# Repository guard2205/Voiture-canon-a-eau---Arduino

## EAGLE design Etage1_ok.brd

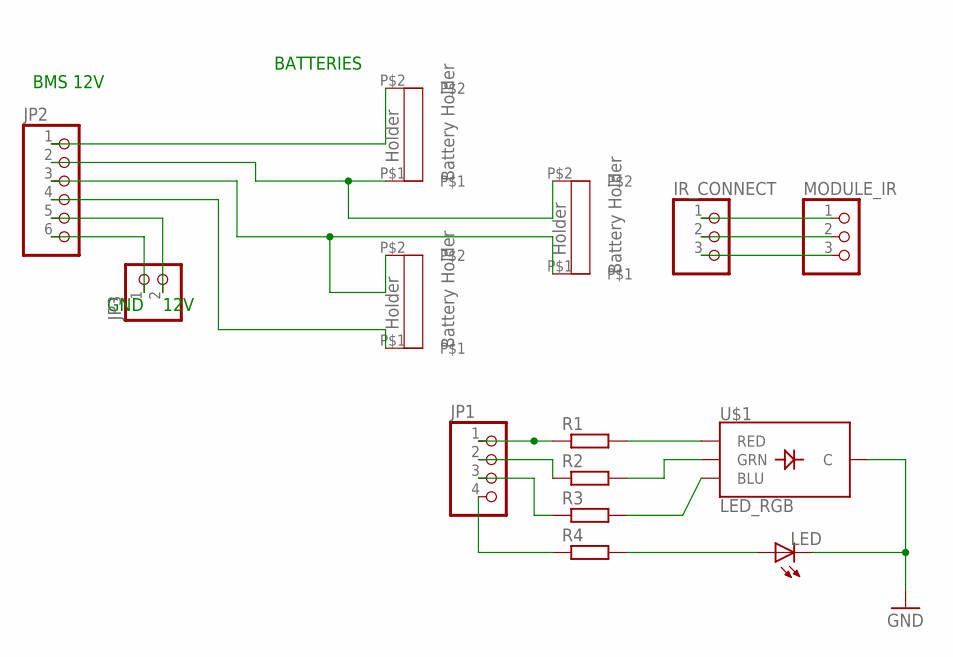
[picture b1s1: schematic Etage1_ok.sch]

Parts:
IR_CONNECT: PINHD-1X3/LONG; 1X03
JP1: PINHD-1X4/LONG; 1X04
JP2: PINHD-1X6/LONG; 1X06
JP3: PINHD-1X2/LONG; 1X02
LED: LED5MM
MODULE_IR: PINHD-1X3/LONG; 1X03
R1, R2, R3, R4: R-EU_0207/10; 0207/10
U$1: LED_RGB; LED-RGB-THRU
U$2, U$3, U$4: SUPPORT_BATTERY; BATTERY_HOLDER

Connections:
GND: LED.K (C), U$1.2 (C)
unnamed: JP2.1, U$4.P$2
unnamed: IR_CONNECT.1, MODULE_IR.1
unnamed: JP2.3, U$2.P$1, U$3.P$2
unnamed: JP2.5, JP3.2
unnamed: JP2.4, U$3.P$1
unnamed: JP2.6, JP3.1
unnamed: R1.2, U$1.4 (RED)
unnamed: R2.2, U$1.3 (GRN)
unnamed: IR_CONNECT.2, MODULE_IR.2
unnamed: JP1.1, R1.1
unnamed: R3.2, U$1.1 (BLU)
unnamed: LED.A, R4.2
unnamed: JP1.4, R4.1
unnamed: JP1.2, R2.1
unnamed: IR_CONNECT.3, MODULE_IR.3
unnamed: JP1.3, R3.1
unnamed: JP2.2, U$2.P$2, U$4.P$1

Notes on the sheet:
BATTERIES
BMS 12V
12V
GND

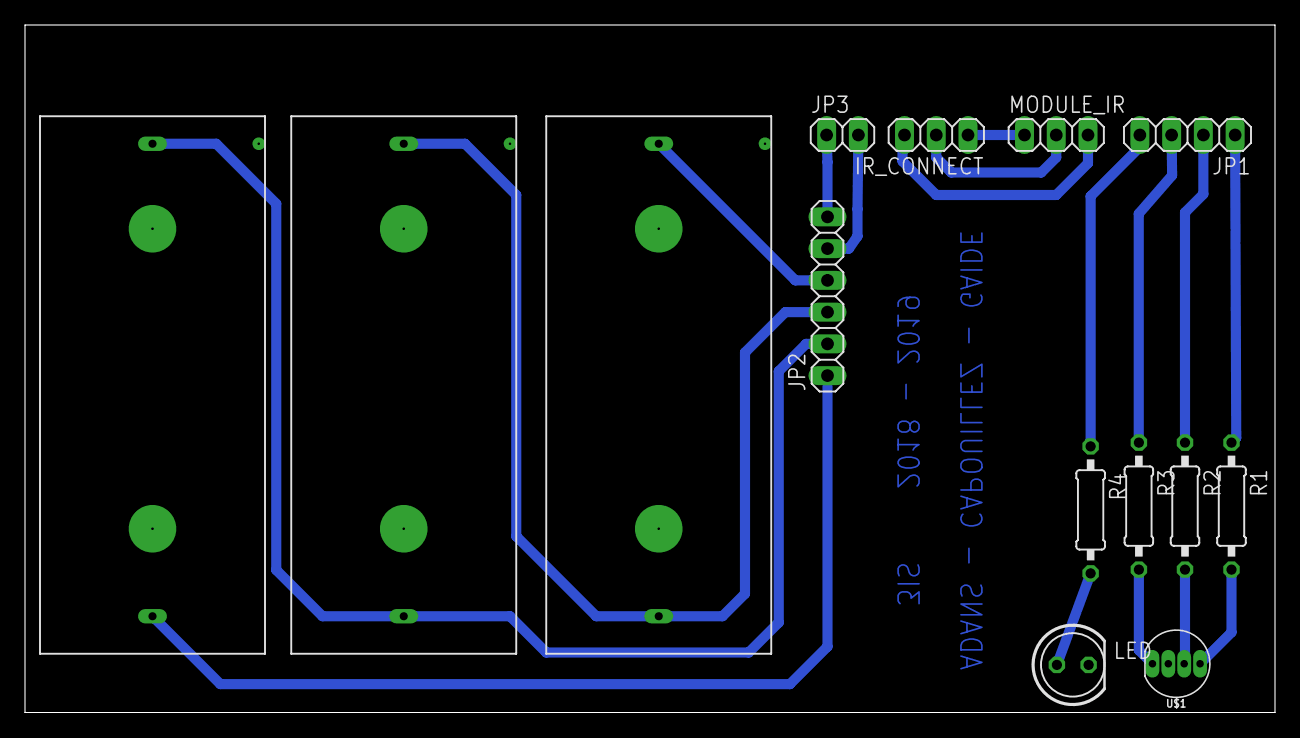
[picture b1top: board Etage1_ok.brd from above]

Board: 2 copper layers, 100.0 x 55.0 mm, 14 parts (0 on the bottom side), 18 nets.

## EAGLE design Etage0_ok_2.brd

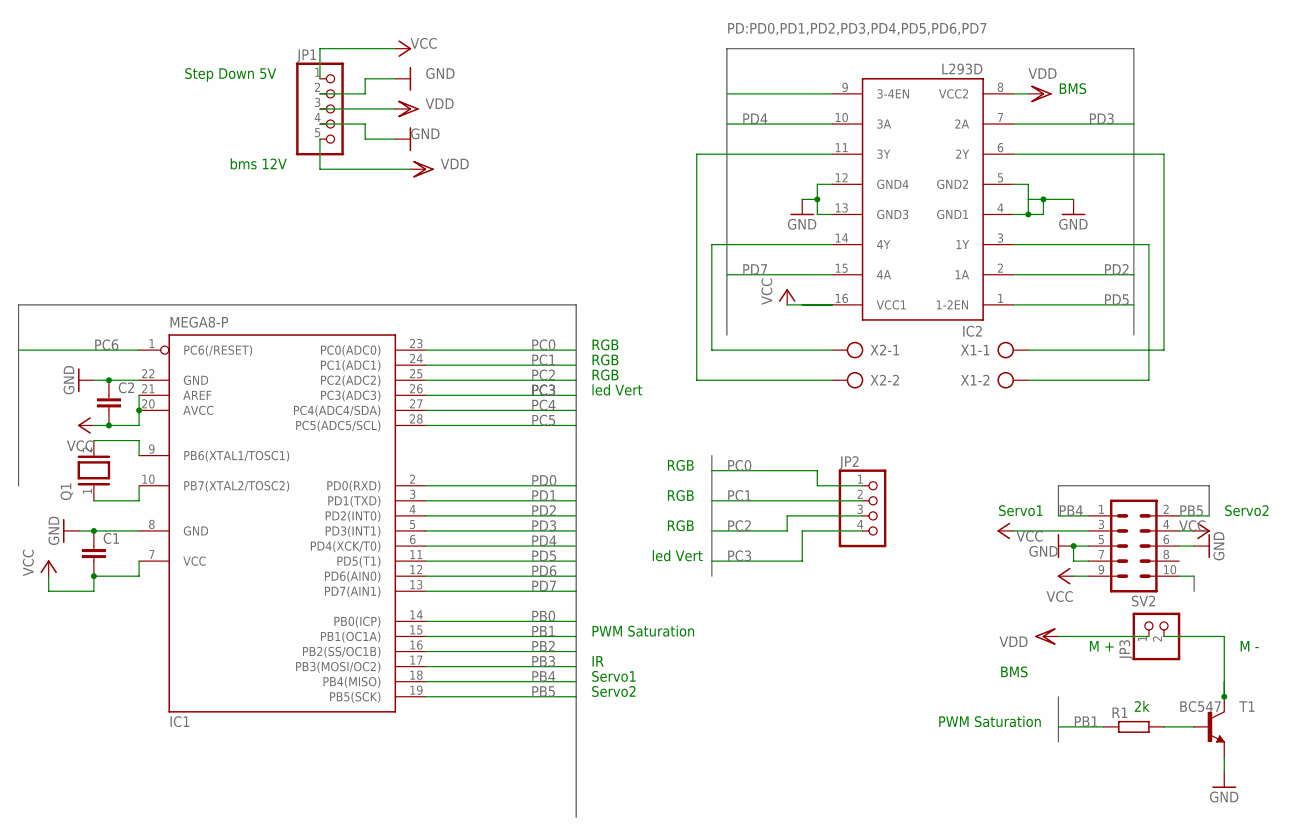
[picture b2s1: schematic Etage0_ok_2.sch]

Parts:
C1, C2: C-EUC1206; C1206
IC1: MEGA8-P; DIL28-3
IC2: L293D; DIL16
JP1: PINHD-1X5; 1X05
JP2: PINHD-1X4; 1X04
JP3: PINHD-1X2; 1X02
Q1: XTAL; Q
R1: R-EU_0204/7; 0204/7
SV2: MA05-2
T1: BC547; TO92
X1, X2: AK300/2

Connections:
GND: C1.1, C2.1, IC1.8 (GND), IC1.22 (GND), IC2.4 (GND1), IC2.5 (GND2), IC2.12 (GND4), IC2.13 (GND3), JP1.2, JP1.4, SV2.5, SV2.6, SV2.7, T1.1 (E)
unnamed: IC1.9 (PB6(XTAL1/TOSC1)), Q1.2
unnamed: IC2.14 (4Y), X2.1
unnamed: IC2.11 (3Y), X2.2
unnamed: IC2.6 (2Y), X1.1
unnamed: IC2.3 (1Y), X1.2
unnamed: R1.2, T1.2 (B)
unnamed: JP3.2, T1.3 (C)
unnamed: IC1.10 (PB7(XTAL2/TOSC2)), Q1.1
PB0: IC1.14 (PB0(ICP))
PB1: IC1.15 (PB1(OC1A)), R1.1
PB2: IC1.16 (PB2(SS/OC1B))
PB3: IC1.17 (PB3(MOSI/OC2)), SV2.10
PB4: IC1.18 (PB4(MISO)), SV2.1
PB5: IC1.19 (PB5(SCK)), SV2.2
PC0: IC1.23 (PC0(ADC0)), JP2.1
PC1: IC1.24 (PC1(ADC1)), JP2.2
PC2: IC1.25 (PC2(ADC2)), JP2.3
PC3: IC1.26 (PC3(ADC3)), JP2.4
PC4: IC1.27 (PC4(ADC4/SDA))
PC5: IC1.28 (PC5(ADC5/SCL))
PC6: IC1.1 (PC6(/RESET))
PD0: IC1.2 (PD0(RXD))
PD1: IC1.3 (PD1(TXD))
PD2: IC1.4 (PD2(INT0)), IC2.2 (1A)
PD3: IC1.5 (PD3(INT1)), IC2.7 (2A)
PD4: IC1.6 (PD4(XCK/T0)), IC2.10 (3A)
PD5: IC1.11 (PD5(T1)), IC2.1 (1-2EN)
PD6: IC1.12 (PD6(AIN0)), IC2.9 (3-4EN)
PD7: IC1.13 (PD7(AIN1)), IC2.15 (4A)
VCC: C1.2, C2.2, IC1.7 (VCC), IC1.20 (AVCC), IC1.21 (AREF), IC2.16 (VCC1), JP1.1, SV2.3, SV2.4, SV2.9
VDD: IC2.8 (VCC2), JP1.3, JP1.5, JP3.1

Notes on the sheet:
M -
M +
BMS
PWM Saturation
led Vert
RGB
Servo1
Servo2
bms 12V
Step Down 5V

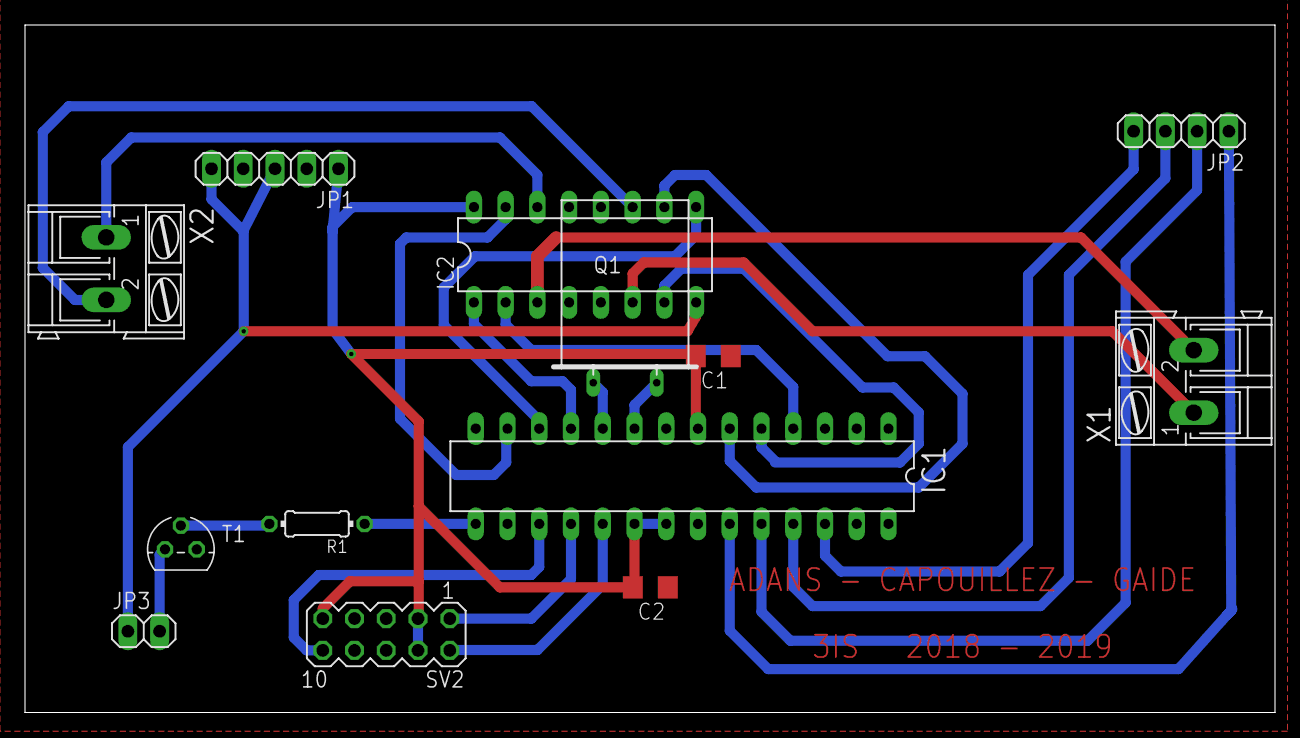
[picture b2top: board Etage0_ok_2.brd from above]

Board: 2 copper layers, 100.0 x 55.0 mm, 13 parts (0 on the bottom side), 25 nets.

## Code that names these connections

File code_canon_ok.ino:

#include <boarddefs.h>
#include <IRremote.h>
#include <IRremoteInt.h>
#include <ir_Lego_PF_BitStreamEncoder.h>
#include <IRRemote.h> 
#include <Servo.h>


// Récepteur IR
int RECV_PIN = 11;  //  PB3
IRrecv irrecv(RECV_PIN);
decode_results results;

// Servo
Servo servoGD;
int angleGD=90;
int pinServo=13;  // PB5

// Moteurs 1=gauche et 2=droite 
int pin1Moteur1=2;  // cmd 1 du moteur 1 PD2
int pin2Moteur1=3;  // cmd 2 du moteur => 1 PD3
int pinPMoteur1=5;  // PMM du moteur 1 => PD5

int pin1Moteur2=4;  //  cmd 1 du moteur 2 =>PD4
int pin2Moteur2=7;  //  cmd 2 du moteur 2 => PD7
int pinPMoteur2=6;  //  PWM du moteur 2  => PD6

int puissanceMax=100;
int puissanceMoy=25;

// Leds
const int ledverte = 17;  // PC3
const byte PIN_LED_R = 16; // PC2
const byte PIN_LED_G = 15; // PC1
const byte PIN_LED_B = 14; // PC0

const byte COLOR_BLACK = 0b000;
const byte COLOR_RED = 0b100;
const byte COLOR_GREEN = 0b010;
const byte COLOR_BLUE = 0b001;
const byte COLOR_MAGENTA = 0b101;
const byte COLOR_CYAN = 0b011;
const byte COLOR_YELLOW = 0b110;
const byte COLOR_WHITE = 0b111;

// Pompe
int pinTransistorBase=9; //PMM du transistor => PB1


void setup()
{  
  Serial.begin(9600);
  irrecv.enableIRIn(); // Start the receiver

  // Règle les servos  
  servoGD.attach(pinServo);
  servoGD.write(angleGD);

 // Règle les pins des moteurs
  pinMode(pin1Moteur1,OUTPUT);
  pinMode(pin2Moteur1,OUTPUT);
  pinMode(pinPMoteur1,OUTPUT);
  pinMode(pin1Moteur2,OUTPUT);
  pinMode(pin2Moteur2,OUTPUT);
  pinMode(pinPMoteur2,OUTPUT);
  int vitesseM1=0; //variable de pourcentage de vitesse pour moteur 1
  int sensM1=1; //variable de sens pour moteur 1
  int vitesseM2=0; //variable de pourcentage de vitesse pour moteur 2
  int sensM2=1; //variable de sens pour moteur 2

  // LEDS
  pinMode(ledverte, OUTPUT);
  pinMode(PIN_LED_R, OUTPUT);
  pinMode(PIN_LED_G, OUTPUT);
  pinMode(PIN_LED_B, OUTPUT);
}

void loop()
{
  digitalWrite(ledverte, HIGH);  // La LED verte s'allume en permanence pour s'assurer que le canon est bien alimenté
  DisplayColor(COLOR_BLACK);  // La LED RGB est éteinte
  
  if (irrecv.decode(&results))  // Dès qu'on reçoit un signal IR, on fait un switch
  {
     Serial.println(results.value, HEX);
     switch(results.value)
     {
        case 0xFFE01F:
        case 0x41C2393C: 
        case 0xF076C13B: Serial.println("tourner tourelle -> gauche");
                         DisplayColor(COLOR_BLUE);
                         TournerGaucheTourelle();
                         delay(500);
                         break;
        case 0x872CD4C:
        case 0xFFA857: 
        case 0x4B05DA56: Serial.println("tourner tourelle -> droite");
                         DisplayColor(COLOR_BLUE);
                         TournerDroiteTourelle();
                         delay(500);
                         break;
        case 0xFF906F:
        case 0xE5CFBD7F: Serial.println("TIR");
                         DisplayColor(COLOR_WHITE);
                         analogWrite(pinTransistorBase, 255);
                         delay(3000);
                         analogWrite(pinTransistorBase, 0);
                         break;
        case 0xFFA25D:
        case 0xE318261B: Serial.println("avancer");
                         DisplayColor(COLOR_GREEN);
                         VoitureAvancer();
                         delay(500);
                         break;
        case 0x511DBB:
        case 0xFF629D:   Serial.println("reculer");
                         DisplayColor(COLOR_GREEN);
                         VoitureReculer();
                         delay(500);
                         break;
        case 0x20FE4DBB:
        case 0xFFC23D:   Serial.println("arret");
                         DisplayColor(COLOR_GREEN);
                         VoitureArreter();
                         delay(500);
                         break;
        case 0x52A3D41F:
        case 0xFF22DD:   Serial.println("Voiture tourne gauche");
                         DisplayColor(COLOR_CYAN);
                         TournerGaucheVoiture();
                         delay(500);
                         break;
        case 0xFF02FD:
        case 0xD7E84B1B:
        case 0x15CB03C4:
        case 0x62B984D4: Serial.println("Voiture tourne droite");
                         DisplayColor(COLOR_CYAN);
                         TournerDroiteVoiture();
                         delay(500);
                         break;
        default: Serial.println("ERREUR");
                 DisplayColor(COLOR_RED);
                 delay(300);
                 DisplayColor(COLOR_BLACK);
                 delay(300);
                 DisplayColor(COLOR_RED);
                 delay(300);
                 break;
     }
     
     irrecv.resume(); // Receive the next value
  }
}

void TournerGaucheTourelle()
{
  if(angleGD > 0)
      angleGD -=10;
  servoGD.write(angleGD);
  delay(500);
}

void TournerDroiteTourelle()
{
  Serial.println(angleGD);
  if(angleGD < 180)
      angleGD +=10;
  servoGD.write(angleGD);
  Serial.println(angleGD);
  delay(500);
}

void VoitureAvancer()
{
  actionMoteur(1,1,puissanceMax); //commande pour moteur gauche
  actionMoteur(2,1,puissanceMax); //commande pour moteur droite
}

void VoitureReculer()
{
  actionMoteur(1,-1,puissanceMax); //commande pour moteur gauche
  actionMoteur(2,-1,puissanceMax); //commande pour moteur droite
}

void VoitureArreter()
{
  actionMoteur(1,0,puissanceMax); //commande pour moteur gauche
  actionMoteur(2,0,puissanceMax); //commande pour moteur droite
}

void TournerGaucheVoiture()
{
  actionMoteur(1,1,puissanceMax); //commande pour moteur gauche
  actionMoteur(2,0,puissanceMoy); //commande pour moteur droite
}

void TournerDroiteVoiture()
{
  actionMoteur(1,0,puissanceMoy); //commande pour moteur gauche
  actionMoteur(2,1,puissanceMax); //commande pour moteur droite
}

void actionMoteur(int moteur,int sens,int pourcentage){
  int pin1,etat1,pin2,etat2,pinP,puissance; //variable de la fonction
  //test numéro du moteur
  if (moteur==1){
    pin1=pin1Moteur1;
    pin2=pin2Moteur1;
    pinP=pinPMoteur1;
  }
  else {
    pin1=pin1Moteur2;
    pin2=pin2Moteur2;
    pinP=pinPMoteur2;
  }
  //test sens du moteur 1,-1 (sens contrainre) ou tout autre valeur (stoppe le moteur)
  if (sens==1){
    etat1=1;
    etat2=0;
  }
  else if (sens==-1){
    etat1=0;
    etat2=1;
  }
  else {
    etat1=0;
    etat2=0;
  }
  puissance= pourcentage; //map(pourcentage,0,100,0,255);
  analogWrite(pinP,puissance);
  digitalWrite(pin1,etat1);
  digitalWrite(pin2,etat2);
}

void DisplayColor(byte color)
{
  digitalWrite(PIN_LED_R, bitRead(color, 2));
  digitalWrite(PIN_LED_G, bitRead(color, 1));
  digitalWrite(PIN_LED_B, bitRead(color, 0));
}

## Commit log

2018-12-20 Grosse update
    Commit du code en c++
    Réalisation des cartes sur eagle
